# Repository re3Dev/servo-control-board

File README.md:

# servo-control-board
Breakout PCB for connecting external stepper/servo motor drivers.

- Takes digital pins from the Archimajor board (3.3V) and shifts voltage (0-50V) according to input using power drivers. 
- Maximum of 11 motors: 7 external, 4 TMC5160
- Display reads out supplied voltage for redundency.
- Pinout is simple and single-ended. Assuming motor driver takes step/pulse, direction, and enable. Currently no support for HLFB.
- Extra +5V and +3.3V output pins
- The main purpose of the project is to drive external servo motors, but other digital I/O devices can be used.

- Digital pins are taken from Serial 5V+, SC1, SC2, and step/dir header of the Archimajor board:

- NOTE:
  - The step/dir header on the archimajor are used for the last four stepper drivers.
  - These pins can be reassigned for external motors on the breakout board.
  - You cannot simultaneously drive an external motor and use the embedded drivers.

- Design is made to primarily support Teknic Clearpath SD series motors.

- Using single-ended connections (will need to invert logic):
  - A+ = Digital
  - B+ = Digital
  - EN+ = Digital
  - A- = GND
  - B- = GND
  - EN- = GND

- Pinout:
  - Motor1:
    - A+ = PA1
    - B+ = PC2
    - EN+ = PA28
  - Motor2:
    - A+ = PB13
    - B+ = PA0
    - EN+ = PB2
  - Motor3:
    - A+ = PB12
    - B+ = PA5
    - EN+ = PB25
  - Motor4:
    - A+ = PB27
    - B+ = PA3
    - EN+ = PB6
  - Motor5:
    - A+ = PB8
    - B+ = PB22
    - EN+ = PB3
  - Motor6:
    - A+ = PD3
    - B+ = PB24
    - EN+ = PB26
  - Motor7:
    - A+ = PA8
    - B+ = PA9
    - EN+ = PC8

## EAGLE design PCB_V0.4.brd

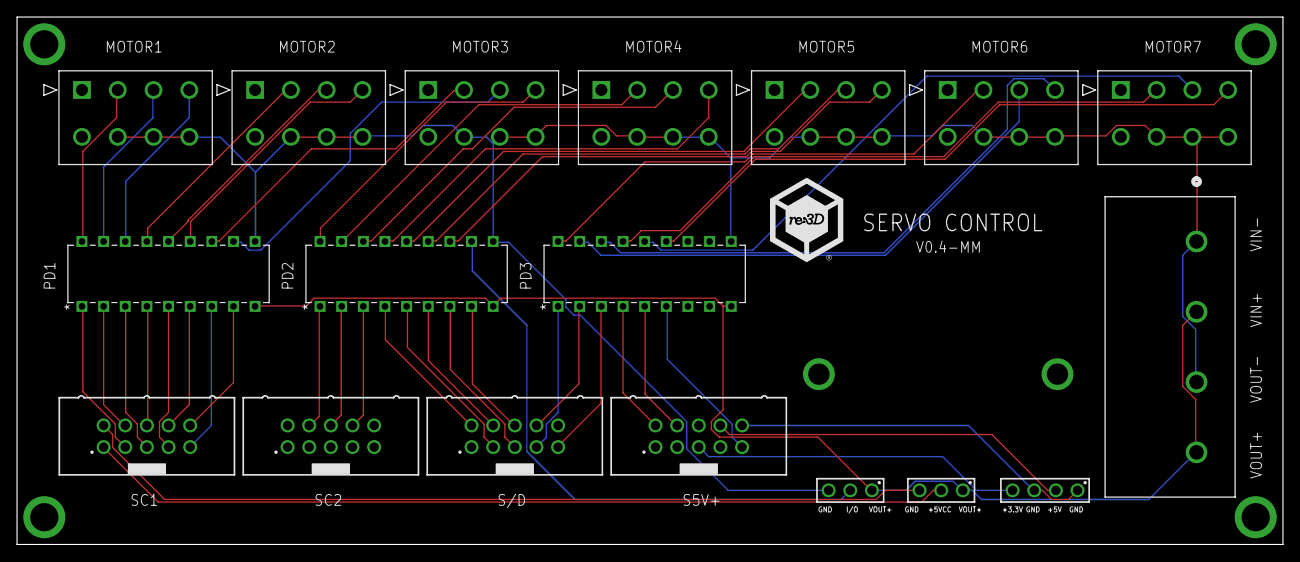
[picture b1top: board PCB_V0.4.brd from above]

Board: 2 copper layers, 148.6 x 61.9 mm, 18 parts (0 on the bottom side), 51 nets.

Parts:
J1, J8: 61300311121
J12: YK3310403000GCONN_YK331040XX00G_AMP; CONN_YK331040XX00G_AMP
J13: 61300411121
MOTOR1, MOTOR2, MOTOR3, MOTOR4, MOTOR5, MOTOR6, MOTOR7: 1724470208CON_1724470208; CON_1724470208
PD1, PD2, PD3: MIC2981/82YNPDIP18_N_MCH; PDIP18_N_MCH
S5V+: 61201021621
S/D: 61201021621
SC1, SC2: 61201021621

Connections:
+3.3VCC: J13.4, S5V+.5
+5VCC: J8.2, SC1.1
+5VCC1: J13.2, S5V+.8
A1+: MOTOR1.3, PD1.17
A2+: MOTOR2.3, PD1.14
A3+: MOTOR3.3, PD1.11
A4+: MOTOR4.3, PD2.16
A5+: MOTOR5.3, PD2.13
A6+: MOTOR6.3, PD3.17
A7+: MOTOR7.3, PD3.14
B1+: MOTOR1.2, PD1.18
B2+: MOTOR2.2, PD1.15
B3+: MOTOR3.2, PD1.12
B4+: MOTOR4.2, PD2.17
B5+: MOTOR5.2, PD2.14
B6+: MOTOR6.2, PD3.18
B7+: MOTOR7.2, PD3.15
EN1+: MOTOR1.4, PD1.16
EN2+: MOTOR2.4, PD1.13
EN3+: MOTOR3.4, PD2.18
EN4+: MOTOR4.4, PD2.15
EN5+: MOTOR5.4, PD2.12
EN6+: MOTOR6.4, PD3.16
EN7+: MOTOR7.4, PD3.13
GND: J1.3, J12.1, J12.3, MOTOR1.6, MOTOR1.7, MOTOR1.8, MOTOR2.6, MOTOR2.7, MOTOR2.8, MOTOR3.6, MOTOR3.7, MOTOR3.8, MOTOR4.6, MOTOR4.7, MOTOR4.8, MOTOR5.6, MOTOR5.7, MOTOR5.8, MOTOR6.6, MOTOR6.7, MOTOR6.8, MOTOR7.6, MOTOR7.7, MOTOR7.8, PD1.10, PD2.10, PD3.10
GND1: J13.1, J13.3, S5V+.10
GND2: J8.3, SC1.2
unnamed: J1.2, PD2.11
PA0: PD1.4, SC1.6
PA1: PD1.2, SC1.4
PA3: PD2.2, SC2.6
PA5: PD1.7, SC1.9
PA8: PD3.5, S5V+.4
PA9: PD3.4, S5V+.2
PA28: PD1.3, SC1.5
PB2: PD1.6, SC1.8
PB3: PD2.7, S/D.5
PB6: PD2.4, S/D.2
PB8: PD2.6, S/D.4
PB12: PD1.8, SC1.10
PB13: PD1.5, SC1.7
PB22: PD2.5, S/D.3
PB24: PD3.1, S/D.7
PB25: PD2.1, SC2.4
PB26: PD3.3, S/D.9
PB27: PD2.3, SC2.8
PC2: PD1.1, SC1.3
PC8: PD3.6, S5V+.9
PD1: PD2.8, S/D.6
PD3: PD3.2, S/D.8
VIN+: J1.1, J8.1, J12.2, J12.4, PD1.9, PD2.9, PD3.9

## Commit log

2024-10-17 Add in files.
2024-10-18 Add step file
2024-10-29 Add pictures
2024-10-31 Import V0.3 files
2026-03-13 Update files for 0.4 changes

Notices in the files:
parts and their libraries:
COPYRIGHT: Copyright (C) 2024 Ultra Librarian. All rights reserved.
